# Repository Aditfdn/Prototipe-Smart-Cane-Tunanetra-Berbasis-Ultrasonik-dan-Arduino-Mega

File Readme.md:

<h1 align="center">Rancang Bangun Tongkat Pintar guna Membantu Mobilitas dan Keselamatan Penyandang Tuna Netra Berbasis ATmega2560 melalui Sistem Deteksi Halangan dan Peringatan Getar dalam Mendukung SDG No. 10 dan 11 (Reduced Inequalities & Sustainable Cities)</h1>

## Deskripsi Proyek
Proyek ini mengembangkan **Tongkat Pintar (Smart White Cane)** berbasis **ATmega2560** yang dirancang untuk membantu mobilitas, keselamatan, dan kemandirian penyandang tuna netra dalam beraktivitas sehari-hari. Sistem mengintegrasikan teknologi deteksi lingkungan, peringatan taktil, serta komunikasi darurat secara real-time guna mendukung implementasi **SDG No. 10 (Reduced Inequalities)** dan **SDG No. 11 (Sustainable Cities and Communities)**.

Tongkat pintar ini memanfaatkan **sensor ultrasonik HC-SR04** untuk mendeteksi keberadaan halangan atau rintangan di depan pengguna. Selain itu, **Rain Sensor** digunakan untuk mendeteksi genangan air atau permukaan jalan yang basah sehingga pengguna dapat menghindari area yang berpotensi membahayakan. Informasi dari kedua sensor tersebut diproses oleh **mikrokontroler ATmega2560** dan diterjemahkan menjadi peringatan berupa getaran melalui **Motor Vibrator** serta bunyi melalui **Buzzer**, sehingga dapat dipahami dengan mudah oleh pengguna tuna netra.

Untuk meningkatkan aspek keselamatan, sistem dilengkapi **Panic Button** yang dapat ditekan pengguna ketika berada dalam kondisi darurat. Saat tombol ditekan, mikrokontroler akan mengaktifkan **modul SIM800L** untuk mengirimkan pesan notifikasi darurat ke akun **Telegram** yang telah terhubung sebelumnya. Fitur ini memungkinkan keluarga, pendamping, atau pihak terkait menerima informasi keadaan darurat secara cepat sehingga bantuan dapat segera diberikan.

Dengan menggabungkan sistem deteksi hambatan, deteksi genangan air, peringatan multimodal, dan komunikasi darurat berbasis Telegram, tongkat pintar ini diharapkan mampu meningkatkan aksesibilitas, keamanan, dan kualitas hidup penyandang tuna netra dalam beraktivitas di lingkungan perkotaan yang inklusif dan berkelanjutan.

## Tujuan Proyek

1. Merancang alat bantu jalan adaptif guna meningkatkan mobilitas mandiri dan keamanan penyandang tuna netra di lingkungan luar ruangan (outdoor).
2. Mengintegrasikan sensor ultrasonik (HC-SR04) dan rain sensor untuk mendeteksi rintangan fisik serta genangan air di jalan secara real-time.
3. Menerapkan sistem umpan balik ganda berupa peringatan getar (motor vibrator) dan suara (buzzer) yang intuitif bagi indra peraba dan pendengaran pengguna.
4. Menyediakan fitur keselamatan darurat berbasis GSM (SIM800L) untuk mengirimkan SMS peringatan otomatis secara real-time saat pengguna menekan tombol panik atau terdeteksi jatuh oleh sensor MPU-6050.
5. Mendukung pencapaian target SDGs global, khususnya SDG 9 (Industry, Innovation, and Infrastructure), SDG 10 (Reduced Inequalities), dan SDG 11 (Sustainable Cities and Communities).

## Support By :

> * Dosen Pengampu: Akhmad Hendriawan ST., MT. (NIP. 197501272002121003)
> * Mata Kuliah: Mikrokontroler
> * Program Studi: D4 Teknik Elektronika
> * Politeknik Elektronika Negeri Surabaya

## Anggota Tim

| Foto | NRP | Nama | Jobdesk | Akun |
| :---: | :---: | :---: | :---: | :---: |
|  | 2124600054 | Ferdian Yuly Aditya | Project Manager | [Aditfdn](https://github.com/Aditfdn) |
|  | 2124600039 | Joseph Frederick Tora  | Hardware Specialist | [josephtora](https://github.com/josephtora) |
|  | 2124600052 | Achmad Nico Al Gofir | 3D Designer | [Oc1nn](https://github.com/Oc1nn) |
|  | 2124600055 | Muhammad Zaky Awwaludin Hani | Progammer | [Cheesejek](https://github.com/CheeseJek) |
|  | 2124600050 | Muhammad Rifqy Prasetiyo| UI/UX Designer | [Rifqypaypal](https://github.com/Rifqypaypal) |
|  | 2124600060 | Delvia Pramesti Regita Cahyani | QA | [delviap](https://github.com/delviap) |

### 🎬 Video Iklan & Promosi Produk

Simak video promosi sinematik S-CANE di bawah ini untuk melihat bagaimana teknologi inklusif berbasis ATmega2560 ini bekerja dalam membantu mobilitas mandiri penyandang tunanetra secara nyata:

https://github.com/user-attachments/assets/74869555-962a-41be-98e7-b088846499c1

> 💡 **Informasi Video:** Video promosi ini mencakup latar belakang permasalahan mobilitas disabilitas, visualisasi desain fisik casing 3D, serta demonstrasi langsung penanganan kondisi darurat (SOS) yang terintegrasi dengan Telegram pendamping.

## Komponen

> * Rain Sensor
> * Motor Vibrator
> * Arduino ATmega 2560
> * HC-SR04 / Sensor Ultrasonik
> * MPU-6050 / Sensor Gyroscope
> * Buzzer
> * Button / Panic Button
> * SIM800L

## 🎨 3D Design & Prototyping
Berikut adalah hasil rancangan 3D dari S-CANE yang dikembangkan menggunakan software [Sebutkan Software, misal: Autodesk Inventor]:

| Tampilan Depan | Tampilan Samping |
| :---: | :---: |
|  |  |

> *Catatan: Desain ini dibuat untuk memastikan ergonomi dan penempatan sensor yang optimal pada tongkat.*

## 📱 UI/UX Design & Simulasi Sistem

Untuk mendukung fungsionalitas S-CANE, dikembangkan juga sebuah konsep antarmuka (UI/UX) aplikasi mobile yang berfungsi sebagai pusat kendali, monitoring status baterai, serta pelacakan lokasi pengguna tongkat secara real-time.

### 🎨 Alur Kerja Antarmuka (User Flow)
Sistem antarmuka dirancang dengan mengutamakan aksesibilitas tinggi dan kemudahan navigasi bagi keluarga atau pendamping tunanetra:

1. **Dashboard Utama:** Menampilkan status konektivitas tongkat, indikator baterai ATmega2560, dan kondisi cuaca di sekitar pengguna (terintegrasi dengan *Rain Sensor*).
2. **Sistem Notifikasi Darurat:** Antarmuka khusus yang akan memicu alarm di sisi pendamping secara otomatis ketika *Panic Button* pada tongkat ditekan atau saat sensor MPU-6050 mendeteksi pengguna terjatuh.
3. **Integrasi Telegram Bot:** Simulasi pengiriman data koordinat dan pesan teks otomatis dari modul SIM800L ke aplikasi Telegram.

### 📐 Galeri Antarmuka
| Splash Screen & Login | Dashboard Monitoring | Notifikasi Darurat |
| :---: | :---: | :---: |
|  |  |  |

### 📱 Panduan Penggunaan Aplikasi Mobile (UI/UX)

Desain antarmuka aplikasi mobile S-CANE tersedia secara lengkap dan interaktif di Figma. Aplikasi ini berfungsi sebagai pusat kendali bagi keluarga atau pendamping tunanetra untuk memantau kondisi pengguna tongkat secara real-time.

🔗 **Akses Desain Figma:** [S-CANE Design Mobile – Figma](https://www.figma.com/design/aeiLbA82CAR6ZKnhpcHcCP/S-CANE-Design-Mobile?node-id=0-1&t=lzUT9AXG1RDVlpGS-0)

### 🗺️ Alur Penggunaan Aplikasi

#### 1. 🚀 Splash Screen & Login
- Buka aplikasi, tampilan *splash screen* S-CANE akan muncul secara otomatis.
- Masukkan acc dan password kalian serta masukkan identitas kalian yang berisikan nama dan nomor (terdaftar telegram).
- Setelah autentikasi berhasil, pengguna akan diarahkan ke halaman **Dashboard Utama**.

#### 2. 📊 Dashboard Monitoring
- Dashboard menampilkan **status koneksi** antara aplikasi dan perangkat S-CANE secara real-time.
- Tersedia indikator **level baterai** ATmega2560 agar pendamping mengetahui kapan perangkat perlu diisi ulang.
- Kondisi lingkungan sekitar pengguna (basah/kering) yang terdeteksi oleh *Rain Sensor* ditampilkan sebagai **status cuaca jalan**.
- Seluruh informasi diperbarui secara otomatis tanpa perlu me-*refresh* halaman.

#### 3. 🆘 Sistem Notifikasi Darurat
- Ketika pengguna menekan **Panic Button** pada tongkat, aplikasi akan langsung menerima notifikasi darurat yang dikirim melalui modul **SIM800L** via Telegram.
- Notifikasi yang sama juga dipicu secara otomatis apabila sensor **MPU-6050** mendeteksi kondisi pengguna terjatuh.
- Halaman notifikasi darurat menampilkan **waktu kejadian**, **status peringatan**, serta panduan tindakan yang dapat segera diambil oleh pendamping.

#### 4. 🤖 Integrasi Telegram Bot
- Semua pesan darurat dan data status dikirimkan secara otomatis ke **akun Telegram** yang telah ditautkan pada saat login.
- Pastikan koneksi internet pada perangkat SIM800L aktif agar notifikasi dapat terkirim tanpa hambatan.
- Pendamping tidak perlu membuka aplikasi secara manual — notifikasi Telegram akan muncul langsung di layar kunci perangkat pendamping.

### ⚙️ Persyaratan Penggunaan
- Akun Telegram yang aktif untuk menerima notifikasi darurat.
- Kartu SIM dengan kuota data aktif yang terpasang pada modul **SIM800L** di perangkat S-CANE.
- Pastikan perangkat S-CANE dalam kondisi menyala dan baterai terisi cukup sebelum digunakan.

> 💡 **Catatan:** Seluruh tampilan antarmuka di atas merupakan konsep desain UI/UX yang dapat diakses dan dieksplorasi secara interaktif melalui tautan Figma di atas. Implementasi aplikasi mobile secara penuh merupakan pengembangan lanjutan dari proyek ini.

### 🎥 Video Simulasi & Demo UI/UX
Berikut adalah video demonstrasi interaktif prototipe dan jalannya aplikasi pendukung S-CANE:

https://github.com/user-attachments/assets/26122700-60ff-4c79-a8bb-ca77b9de54d8

## 🎬 Video Simulasi Sistem Keseluruhan

Selain pemodelan antarmuka, pengujian fungsionalitas logika program ATmega2560 pada proyek S-CANE ini juga didokumentasikan melalui simulasi interaktif. Video ini menampilkan bagaimana seluruh sensor (HC-SR04, Rain Sensor, MPU-6050) merespons lingkungan dan mengirimkan data secara sinkron ke aktuator serta sistem peringatan.

### 🕹️ Link Simulasi Aktif (Wokwi)

Anda dapat melihat, menjalankan, dan menguji logika program ATmega2560 pada sirkuit S-CANE secara langsung melalui browser tanpa perlu perangkat keras fisik. Klik tombol di bawah ini untuk membuka simulator:

> 💡 **Cara Menguji Alat di Wokwi:**
> 1. Klik tombol **Launch Wokwi Simulator** di atas.
> 2. Klik tombol **Start Simulation (Ikon Play Hijau)** pada halaman Wokwi.
> 3. Klik pada komponen **HC-SR04** untuk menggeser slider jarak halangan, atau tekan **Panic Button** untuk melihat respons dari Buzzer dan Motor Vibrator, klik **MPU** untuk melihat kemiringan gyroscope, serta 2 **Potensio** yang satu sebelah kiri **Rain Sensor** dan sebelah kanan sebagai Data Dummy baterai pada **UI/UX** .

### 📺 Demo Simulasi Alat

https://github.com/user-attachments/assets/4040b269-2278-43a4-b501-594f7b9bb5d2

> 💡 **Informasi Pengujian:** > * **Simulasi Input:** Simulasi pembacaan jarak rintangan dan deteksi kondisi jalan basah/genangan air.
> * **Simulasi Output:** Respons kedipan frekuensi buzzer, kekuatan getaran motor vibrator, serta simulasi pengiriman instruksi AT Command oleh modul GSM SIM800L.

## ⚙️ Simulasi Sistem Keseluruhan

Pengujian fungsionalitas dan logika program **ATmega2560** pada proyek S-CANE didokumentasikan sepenuhnya melalui rekaman video simulasi. Video ini menampilkan bagaimana seluruh sistem dari 3D, Ui Ux hingga sensor (HC-SR04, Rain Sensor, MPU-6050) merespons lingkungan dan berinteraksi secara sinkron dengan komponen output.

### 🎥 Video Demonstrasi Simulasi Alat
Berikut adalah rekaman jalannya pengujian simulasi sistem S-CANE dari awal hingga akhir:

https://github.com/user-attachments/assets/8619169c-2171-4413-95fd-638ff369f83f

---

### 🔍 Cakupan Pengujian dalam Video:
* **Simulasi Deteksi Rintangan:** Demonstrasi respons frekuensi suara *Buzzer* dan kekuatan *Motor Vibrator* saat sensor ultrasonik HC-SR04 mendeteksi objek dalam jarak dekat dan kritis.
* **Simulasi Deteksi Cuaca/Jalan Basah:** Respons sistem saat *Rain Sensor* mendeteksi adanya genangan air atau permukaan jalan yang basah.
* **Simulasi Kondisi Darurat (SOS):** Pengujian logika pengiriman pesan darurat otomatis ke UI/UX dan Telegram pendamping ketika *Panic Button* ditekan atau ketika sensor *MPU-6050* mendeteksi simulasi pengguna terjatuh.

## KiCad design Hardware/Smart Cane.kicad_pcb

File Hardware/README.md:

# Schematic

# 3D View

## Top View

## Bottom View

# PCB Layer

## Front & Back Layer
.jpeg)
## Front Layer
.jpeg)
## Back Layer
.jpeg)

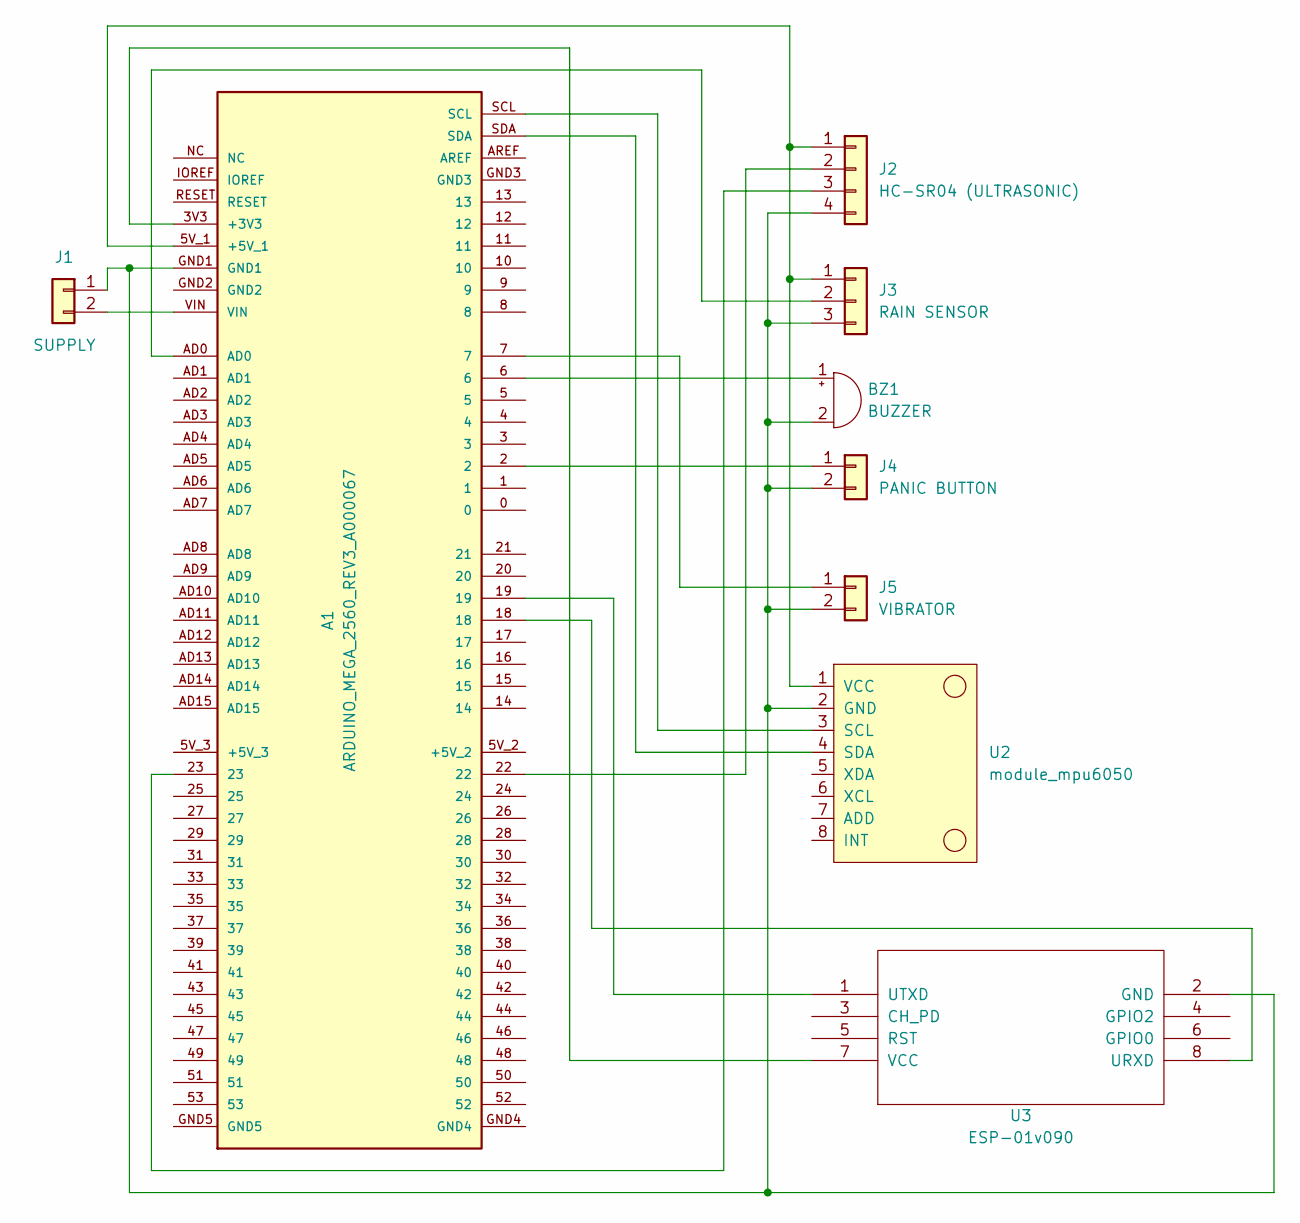
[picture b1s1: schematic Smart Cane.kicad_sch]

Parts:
A1: ARDUINO_MEGA_2560_REV3_A000067; ARDUINO_ARDUINO_MEGA_2560_REV3_A000067; PARTREV 3
BZ1: BUZZER; Buzzer_12x9.5RM7.6
J1: SUPPLY; Stocko_MKS_1652-6-0-202_1x2_P2.50mm_Vertical
J2: HC-SR04 (ULTRASONIC); Stocko_MKS_1654-6-0-404_1x4_P2.50mm_Vertical
J3: RAIN SENSOR; Stocko_MKS_1653-6-0-303_1x3_P2.50mm_Vertical
J4: PANIC BUTTON; Stocko_MKS_1652-6-0-202_1x2_P2.50mm_Vertical
J5: VIBRATOR; Stocko_MKS_1652-6-0-202_1x2_P2.50mm_Vertical
U2: module_mpu6050
U3: ESP-01v090; ESP-01

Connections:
unnamed: A1.3V3 (+3V3), U3.7 (VCC)
unnamed: A1.5V_1 (+5V_1), J2.1, J3.1, U2.1 (VCC)
unnamed: A1.6, BZ1.1 (+)
unnamed: A1.GND1, BZ1.2 (-), J1.1, J2.4, J3.3, J4.2, J5.2, U2.2 (GND), U3.2 (GND)
unnamed: A1.VIN, J1.2
unnamed: A1.22, J2.2
unnamed: A1.23, J2.3
unnamed: A1.AD0, J3.2
unnamed: A1.2, J4.1
unnamed: A1.7, J5.1
unnamed: A1.SCL, U2.3 (SCL)
unnamed: A1.SDA, U2.4 (SDA)
unnamed: A1.18, U3.8 (URXD)
unnamed: A1.19, U3.1 (UTXD)

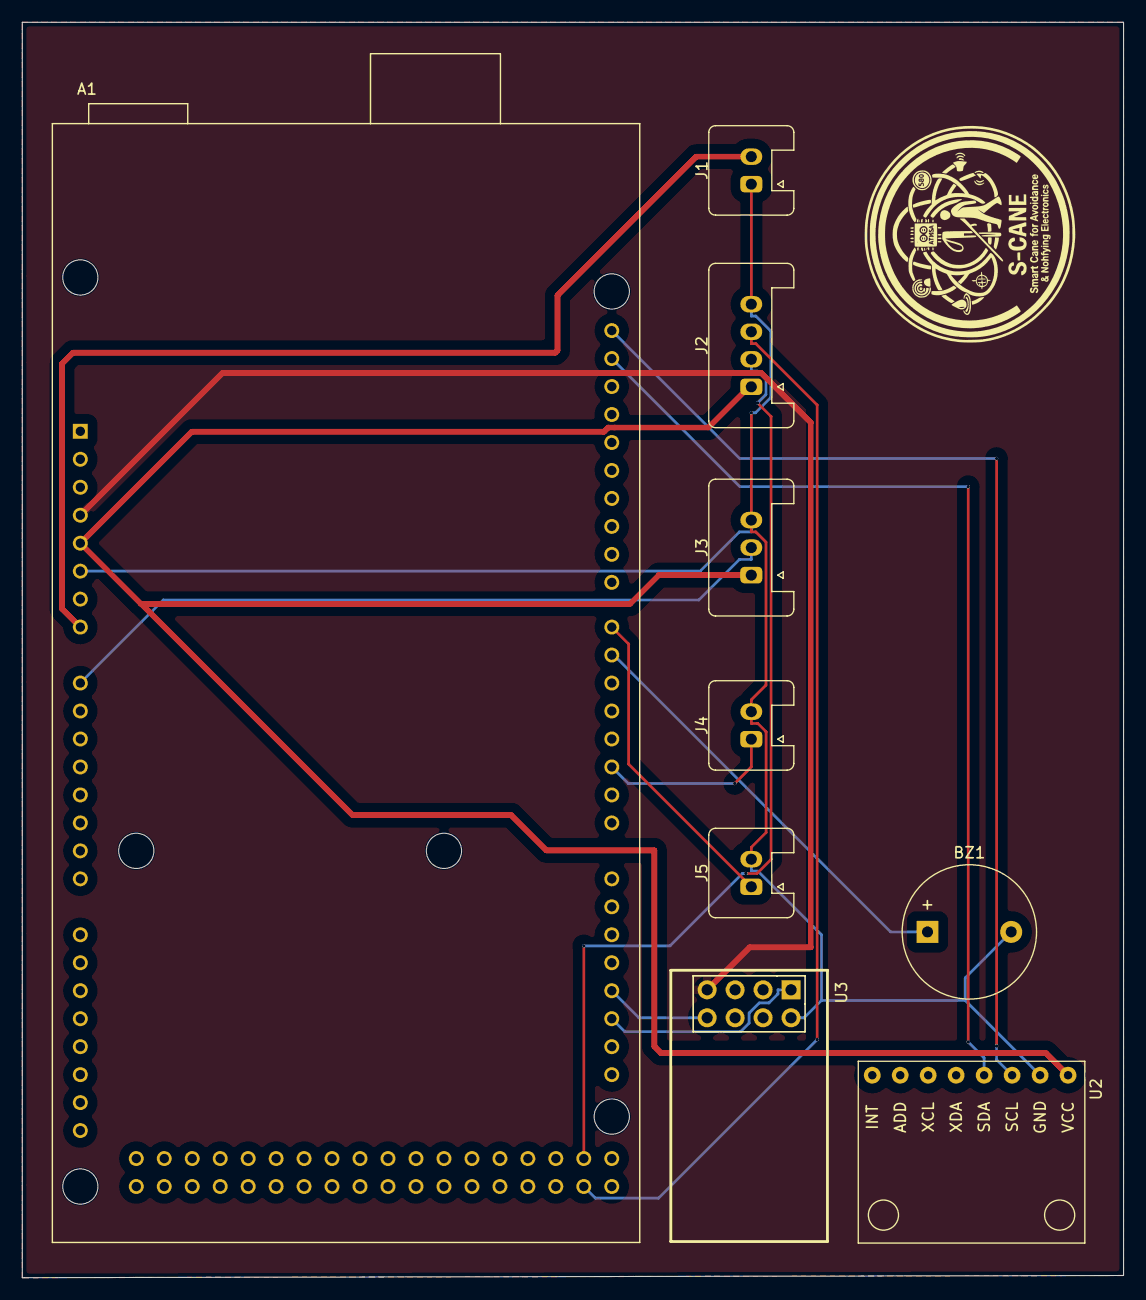
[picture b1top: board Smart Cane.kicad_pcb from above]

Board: 2 copper layers, 100.0 x 114.0 mm, 9 parts (0 on the bottom side), 14 nets.

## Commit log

2026-05-29 Update team member details in Readme.md
    Added Achmad Nico Al Gofir as a 3D Designer.
2026-05-31 Create 3D Design
2026-05-31 Create Foto identitas
2026-05-31 Rename Assets/Foto identitas/readme.md to Assets/readme.md
2026-06-01 Schematic
2026-06-01 Foto Identitas/Asset directory
2026-06-01 Create KiCad Schematic
2026-06-01 KiCad Schematic
2026-06-01 Rename ChatGPT Image Jun 1, 2026, 08_39_41 PM.png to Tabel IO
2026-06-01 Rename IMG-20260601-WA0041.jpg to KiCad Schematic.jpg
2026-06-01 Initialize UI/UX documentation for S-CANE project
2026-06-01 Add UI/UX documentation overview and project structure
2026-06-01 Add application mockups and user flow diagrams
2026-06-03 Update Anggota Tim
2026-06-03 Update Tabel Anggota Kelompok
2026-06-03 Upload foto identitas baru
2026-06-03 Update Foto Identitas
2026-06-03 Rename B.Cu.jpeg to Back Layer (B.Cu).jpeg
2026-06-03 Rename F.Cu & B.Cu.jpeg to Front Layer & Back Layer (F.Cu & B.Cu).jpeg
2026-06-03 Rename F.Cu.jpeg to Front Layer (F.Cu).jpeg
2026-06-04 Upload kicad_sch file
2026-06-04 add kicad_pro and kicad_pcb file
2026-06-07 Create Simulasi
2026-06-07 Create Foto Anggota Kelompok
2026-06-07 Create Photo Preview
2026-06-07 Rename MASTER BOX.png to Master Box.png
2026-06-07 Rename FRONT.PNG to Front.PNG
2026-06-07 Rename LEFT.PNG to Left.PNG
2026-06-07 Rename RAIN SENSOR.PNG to Rain Sensor.PNG
2026-06-07 Rename RIGHT.png to Right.png
2026-06-07 Rename ULTRASONIC CASE.png to Ultrasonic Case.png
